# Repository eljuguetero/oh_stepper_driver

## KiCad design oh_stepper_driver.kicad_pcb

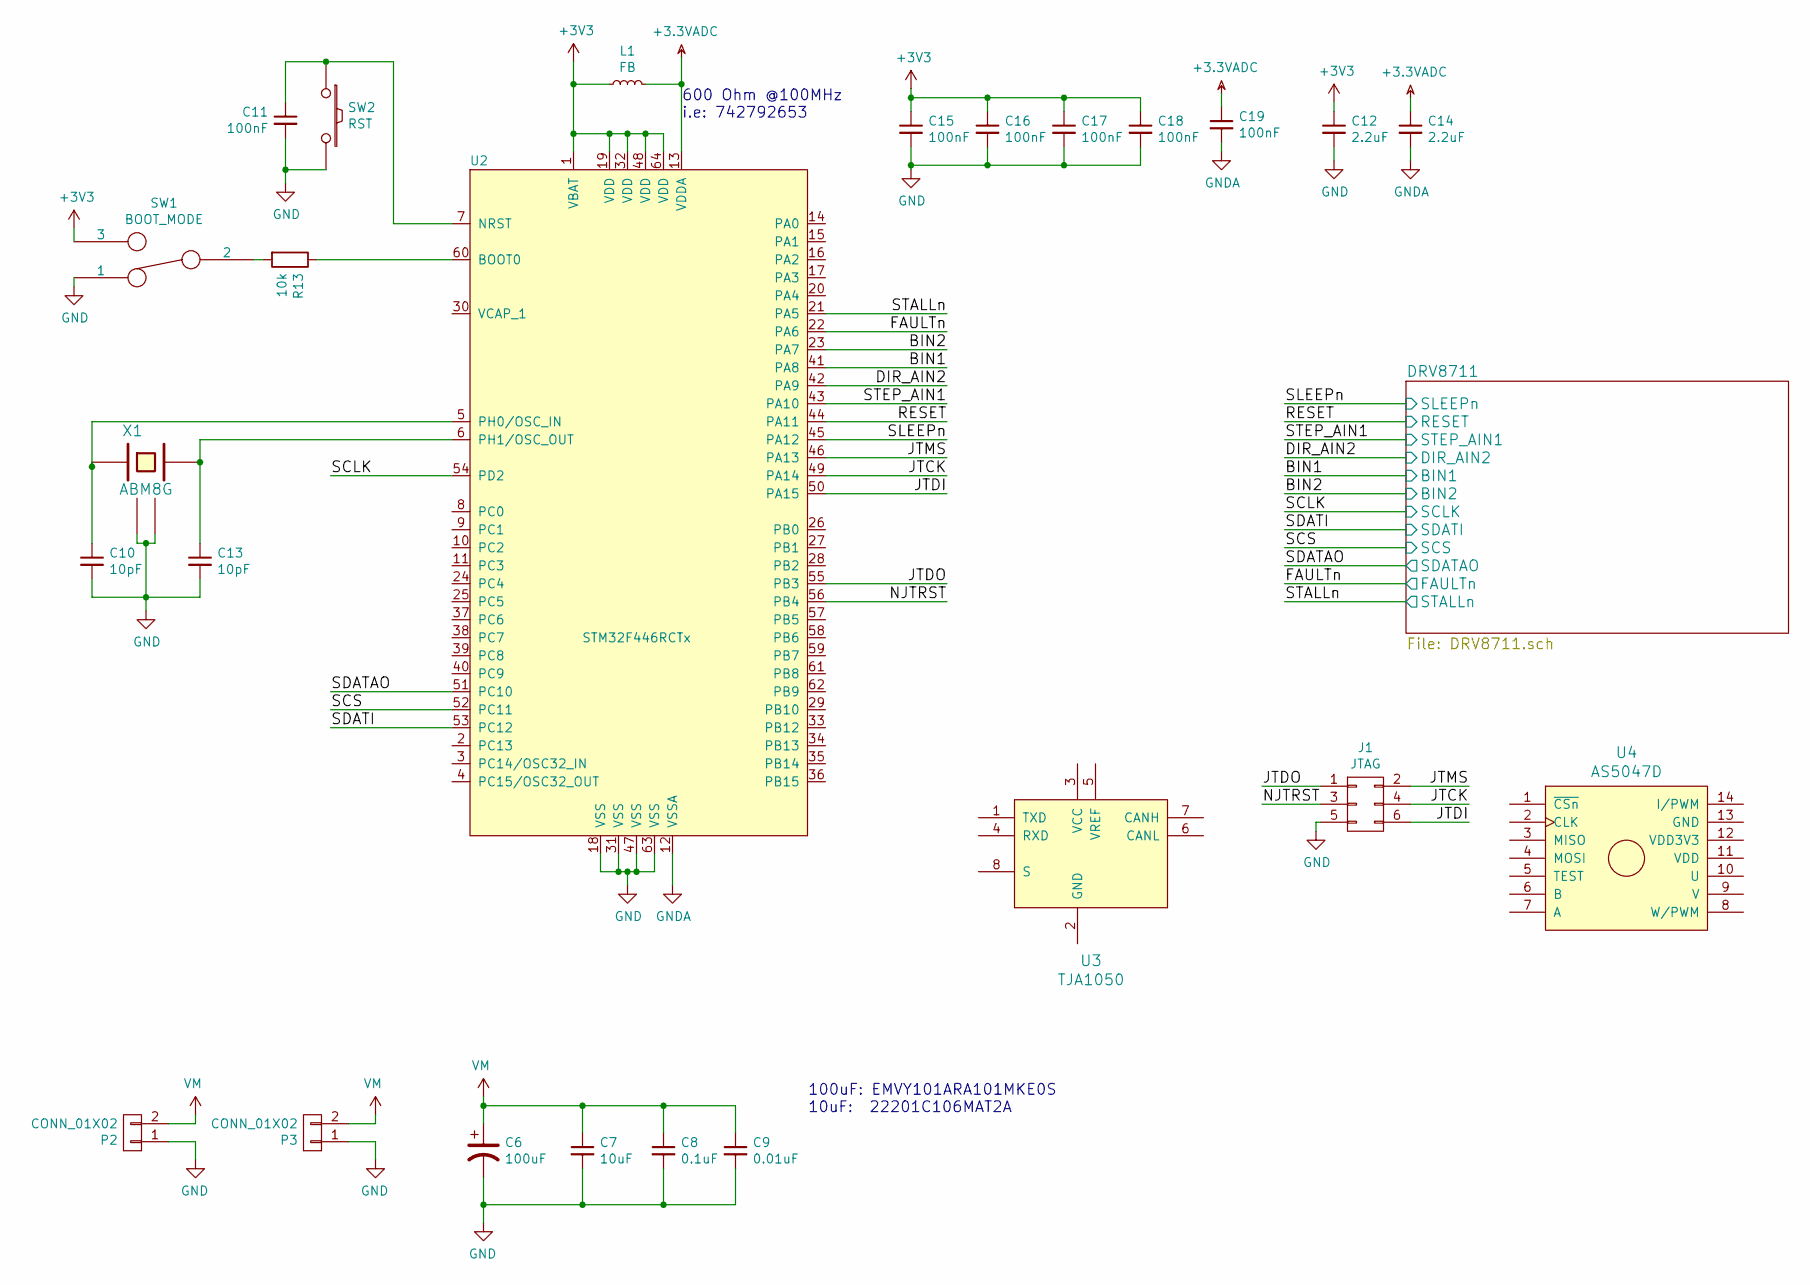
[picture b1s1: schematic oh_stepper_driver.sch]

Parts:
C6: 100uF
C7: 10uF; C_2220
C8: 0.1uF; C_0603
C9: 0.01uF; C_0603
C10, C13: 10pF; C_0402
C11, C15, C16, C17, C18, C19: 100nF; C_0402
C12, C14: 2.2uF; C_0402
J1: JTAG; Pin_Header_Straight_2x03_Pitch2.54mm
L1: FB; R_0603
P2, P3: CONN_01X02; bornier2
R13: 10k; R_0402
SW1: BOOT_MODE; Pin_Header_Straight_1x03_Pitch2.54mm
SW2: RST
U2: STM32F446RCTx; LQFP-64_10x10mm_Pitch0.5mm
U3: TJA1050; SOIC-8-N
U4: AS5047D; SSOP-14
X1: ABM8G

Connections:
+3.3VADC: C14.1, C19.1, L1.2, U2.13 (VDDA)
+3V3: C12.1, C15.1, C16.1, C17.1, C18.1, L1.1, SW1.3, U2.1 (VBAT), U2.19 (VDD), U2.32 (VDD), U2.48 (VDD), U2.64 (VDD)
/BIN1: U2.41 (PA8); also elsewhere on the board
/BIN2: U2.23 (PA7); also elsewhere on the board
/DIR_AIN2: U2.42 (PA9); also elsewhere on the board
/FAULTn: U2.22 (PA6); also elsewhere on the board
/JTCK: J1.4, U2.49 (PA14)
/JTDI: J1.6, U2.50 (PA15)
/JTDO: J1.1, U2.55 (PB3)
/JTMS: J1.2, U2.46 (PA13)
/NJTRST: J1.3, U2.56 (PB4)
/RESET: U2.44 (PA11); also elsewhere on the board
/SCLK: U2.54 (PD2); also elsewhere on the board
/SCS: U2.52 (PC11); also elsewhere on the board
/SDATAO: U2.51 (PC10); also elsewhere on the board
/SDATI: U2.53 (PC12); also elsewhere on the board
/SLEEPn: U2.45 (PA12); also elsewhere on the board
/STALLn: U2.21 (PA5); also elsewhere on the board
/STEP_AIN1: U2.43 (PA10); also elsewhere on the board
GND: C6.2, C7.2, C8.2, C9.2, C10.2, C11.2, C12.2, C13.2, C15.2, C16.2, C17.2, C18.2, J1.5, P2.1, P3.1, SW1.1, SW2.2, U2.18 (VSS), U2.31 (VSS), U2.47 (VSS), U2.63 (VSS), X1.2 (GND), X1.4 (GND); also elsewhere on the board
GNDA: C14.2, C19.2, U2.12 (VSSA)
unnamed: C10.1, U2.5 (PH0/OSC_IN), X1.1
unnamed: C11.1, SW2.1, U2.7 (NRST)
unnamed: C13.1, U2.6 (PH1/OSC_OUT), X1.3
unnamed: R13.1, U2.60 (BOOT0)
unnamed: R13.2, SW1.2
VM: C6.1, C7.1, C8.1, C9.1, P2.2, P3.2; also elsewhere on the board

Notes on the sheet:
100uF: EMVY101ARA101MKE0S 10uF: 22201C106MAT2A
600 Ohm @100MHz i.e: 742792653

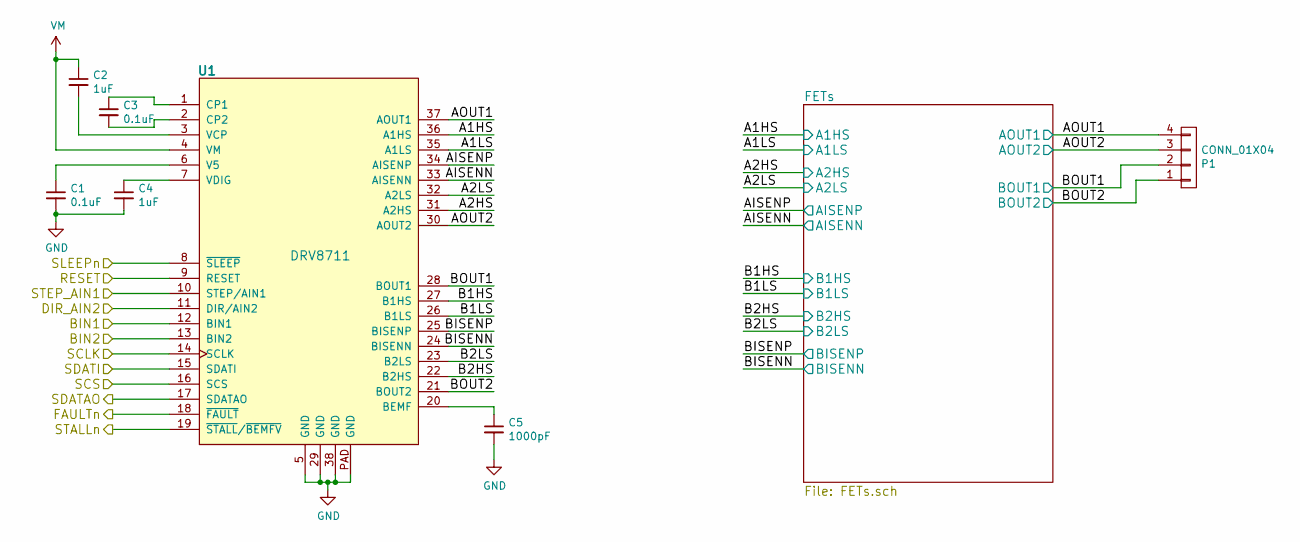
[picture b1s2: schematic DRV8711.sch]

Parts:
C1, C3: 0.1uF; C_0603
C2, C4: 1uF; C_0603
C5: 1000pF; C_0402
P1: CONN_01X04; bornier4
U1: DRV8711; HTSSOP_38_Pitch0.5mm

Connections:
/BIN1: U1.12 (BIN1); also elsewhere on the board
/BIN2: U1.13 (BIN2); also elsewhere on the board
/DIR_AIN2: U1.11 (DIR/AIN2); also elsewhere on the board
/DRV8711/A1HS: U1.36 (A1HS); also elsewhere on the board
/DRV8711/A1LS: U1.35 (A1LS); also elsewhere on the board
/DRV8711/A2HS: U1.31 (A2HS); also elsewhere on the board
/DRV8711/A2LS: U1.32 (A2LS); also elsewhere on the board
/DRV8711/AISENN: U1.33 (AISENN); also elsewhere on the board
/DRV8711/AISENP: U1.34 (AISENP); also elsewhere on the board
/DRV8711/AOUT1: P1.4, U1.37 (AOUT1); also elsewhere on the board
/DRV8711/AOUT2: P1.3, U1.30 (AOUT2); also elsewhere on the board
/DRV8711/B1HS: U1.27 (B1HS); also elsewhere on the board
/DRV8711/B1LS: U1.26 (B1LS); also elsewhere on the board
/DRV8711/B2HS: U1.22 (B2HS); also elsewhere on the board
/DRV8711/B2LS: U1.23 (B2LS); also elsewhere on the board
/DRV8711/BISENN: U1.24 (BISENN); also elsewhere on the board
/DRV8711/BISENP: U1.25 (BISENP); also elsewhere on the board
/DRV8711/BOUT1: P1.2, U1.28 (BOUT1); also elsewhere on the board
/DRV8711/BOUT2: P1.1, U1.21 (BOUT2); also elsewhere on the board
/FAULTn: U1.18 (~FAULT); also elsewhere on the board
/RESET: U1.9 (RESET); also elsewhere on the board
/SCLK: U1.14 (SCLK); also elsewhere on the board
/SCS: U1.16 (SCS); also elsewhere on the board
/SDATAO: U1.17 (SDATAO); also elsewhere on the board
/SDATI: U1.15 (SDATI); also elsewhere on the board
/SLEEPn: U1.8 (~SLEEP); also elsewhere on the board
/STALLn: U1.19 (~STALL~/~BEMFV~); also elsewhere on the board
/STEP_AIN1: U1.10 (STEP/AIN1); also elsewhere on the board
GND: C1.2, C4.2, C5.2, U1.5 (GND), U1.29 (GND), U1.38 (GND), U1.PAD (GND); also elsewhere on the board
unnamed: C1.1, U1.6 (V5)
unnamed: C2.2, U1.3 (VCP)
unnamed: C3.1, U1.1 (CP1)
unnamed: C3.2, U1.2 (CP2)
unnamed: C4.1, U1.7 (VDIG)
unnamed: C5.1, U1.20 (BEMF)
VM: C2.1, U1.4 (VM); also elsewhere on the board

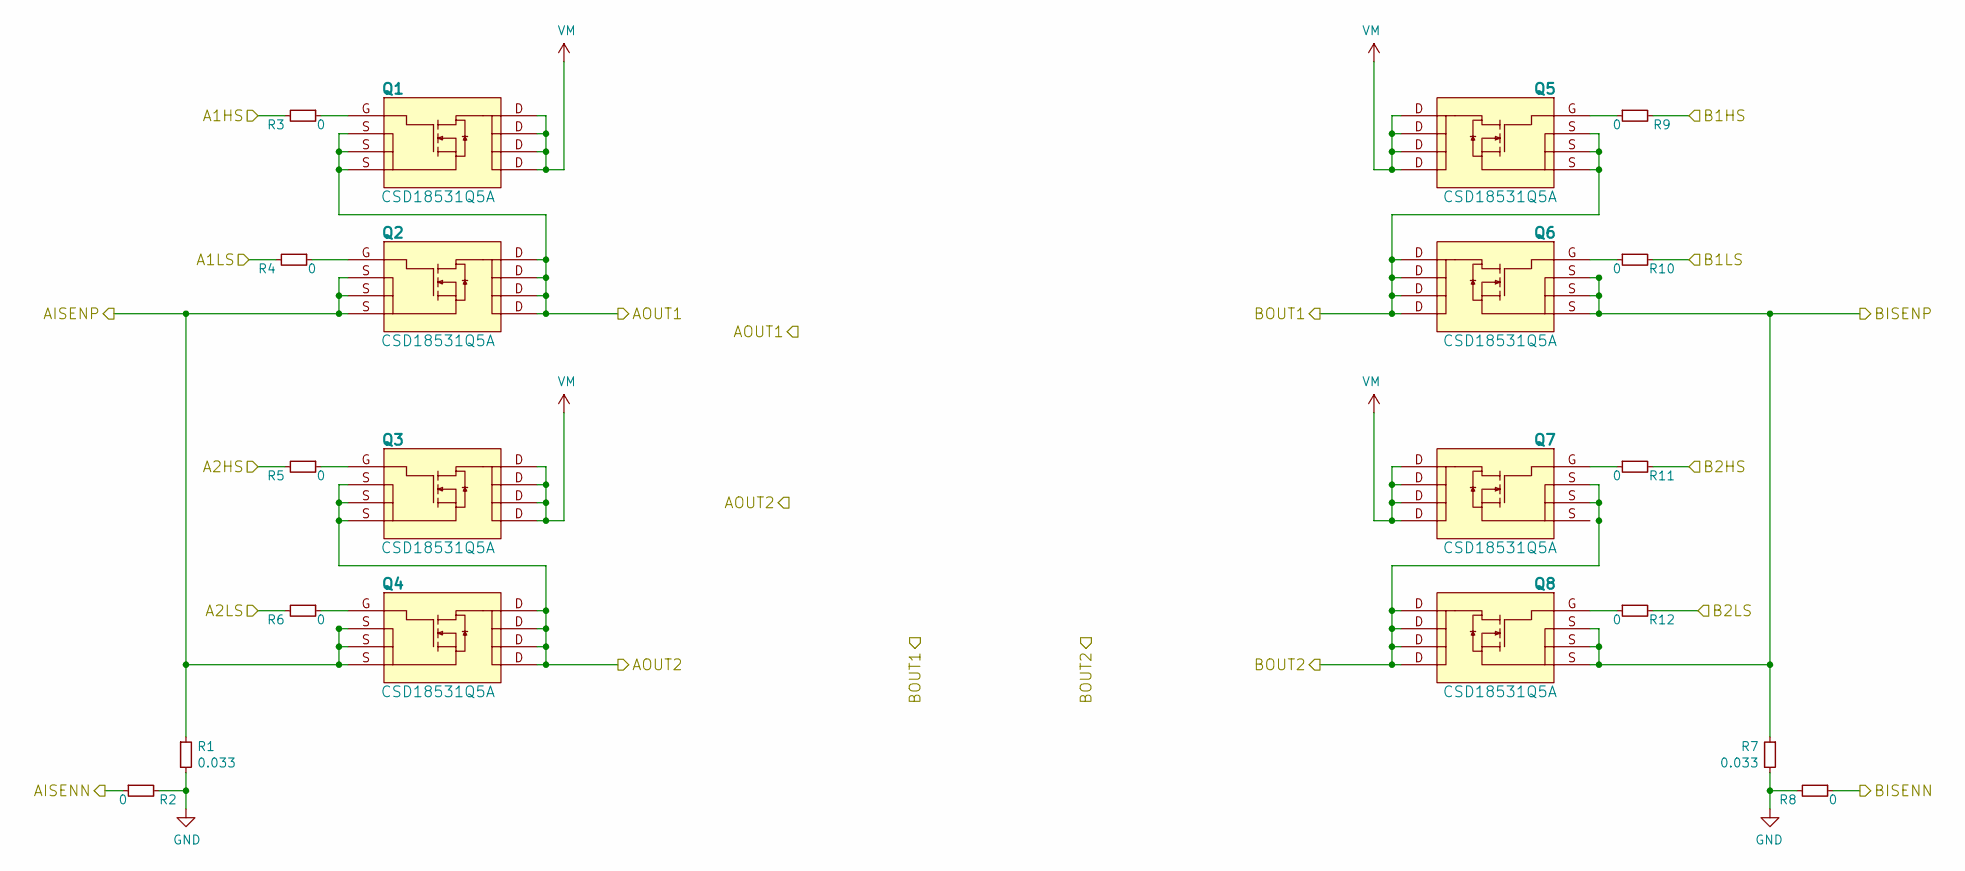
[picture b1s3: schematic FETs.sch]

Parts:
Q1, Q2, Q3, Q4, Q5, Q6, Q7, Q8: CSD18531Q5A; SON5x6_FET
R1, R7: 0.033; R_2816
R2, R8: 0; R_0603
R3, R4, R5, R6, R9, R10, R11, R12: 0; R_0402

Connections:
/DRV8711/A1HS: R3.2; also elsewhere on the board
/DRV8711/A1LS: R4.2; also elsewhere on the board
/DRV8711/A2HS: R5.2; also elsewhere on the board
/DRV8711/A2LS: R6.2; also elsewhere on the board
/DRV8711/AISENN: R2.1; also elsewhere on the board
/DRV8711/AISENP: Q2.S, Q4.S, R1.1; also elsewhere on the board
/DRV8711/AOUT1: Q1.S, Q2.D; also elsewhere on the board
/DRV8711/AOUT2: Q3.S, Q4.D; also elsewhere on the board
/DRV8711/B1HS: R9.2; also elsewhere on the board
/DRV8711/B1LS: R10.2; also elsewhere on the board
/DRV8711/B2HS: R11.2; also elsewhere on the board
/DRV8711/B2LS: R12.2; also elsewhere on the board
/DRV8711/BISENN: R8.1; also elsewhere on the board
/DRV8711/BISENP: Q6.S, Q8.S, R7.1; also elsewhere on the board
/DRV8711/BOUT1: Q5.S, Q6.D; also elsewhere on the board
/DRV8711/BOUT2: Q7.S, Q8.D; also elsewhere on the board
GND: R1.2, R2.2, R7.2, R8.2; also elsewhere on the board
unnamed: Q1.G, R3.1
unnamed: Q2.G, R4.1
unnamed: Q3.G, R5.1
unnamed: Q4.G, R6.1
unnamed: Q5.G, R9.1
unnamed: Q6.G, R10.1
unnamed: Q7.G, R11.1
unnamed: Q8.G, R12.1
VM: Q1.D, Q3.D, Q5.D, Q7.D; also elsewhere on the board

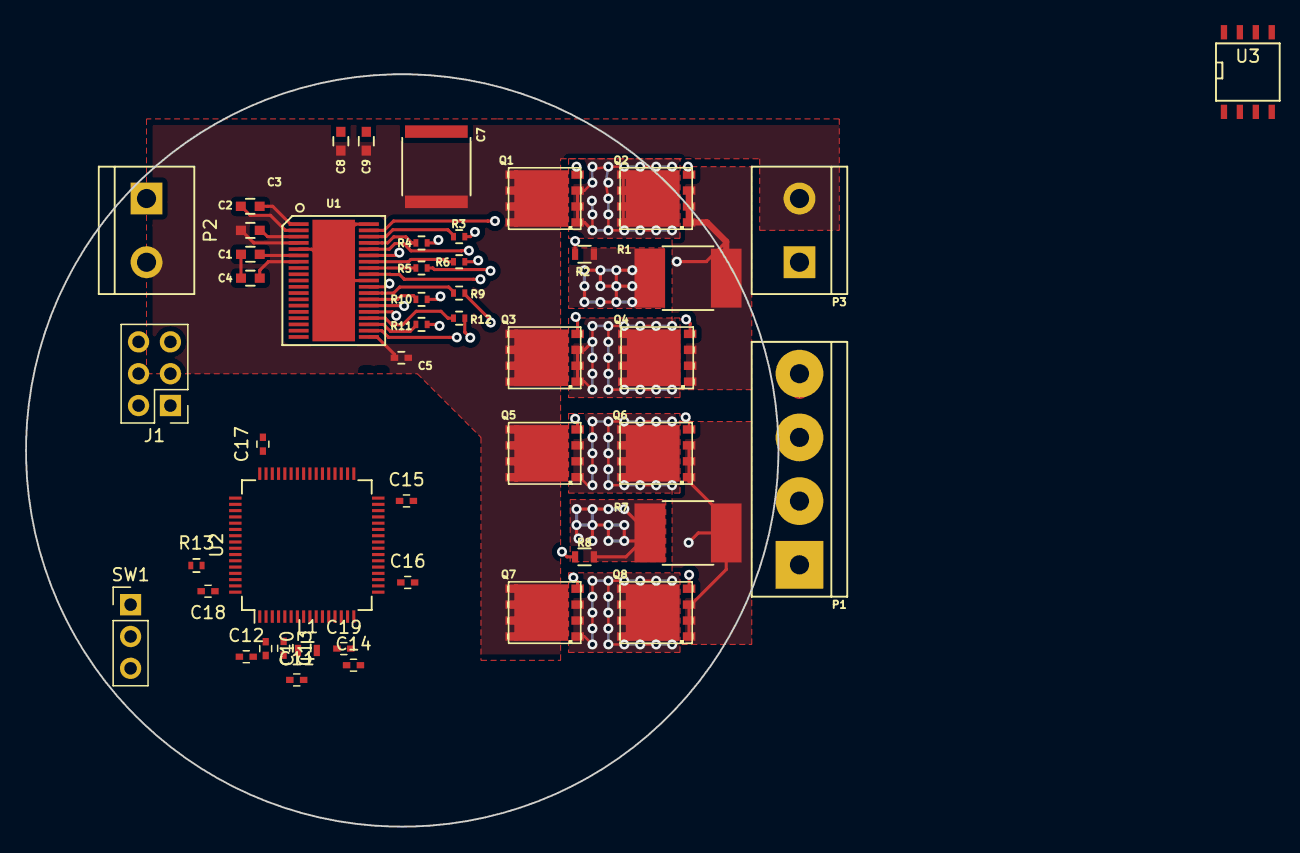
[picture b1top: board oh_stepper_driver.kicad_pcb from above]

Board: 4 copper layers, 60.0 x 60.0 mm, 49 parts (1 on the bottom side), 57 nets.

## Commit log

2017-01-14 Driver started
2017-01-15 FETs sheet added
2017-01-15 stepper draw added
2017-01-15 adding decoupling filters
2017-01-15 adding capacitors to the PCB
2017-01-16 stm32f446 added
2017-01-18 connecting STM32 passives
2017-01-25 connecting control lines between the motor driver and the STM32
2017-02-06 connecting mcu
2017-02-07 fp-lib-table fixed
2017-02-15 routing FETs
2017-02-15 4 layers
2017-02-15 routing control signals
2017-02-16 cooper pour for motor driver
2017-02-18 library of transeiver can
2017-02-19 adding encoder
2017-02-19 encoder placement
2018-05-07 KiCAD version updated
